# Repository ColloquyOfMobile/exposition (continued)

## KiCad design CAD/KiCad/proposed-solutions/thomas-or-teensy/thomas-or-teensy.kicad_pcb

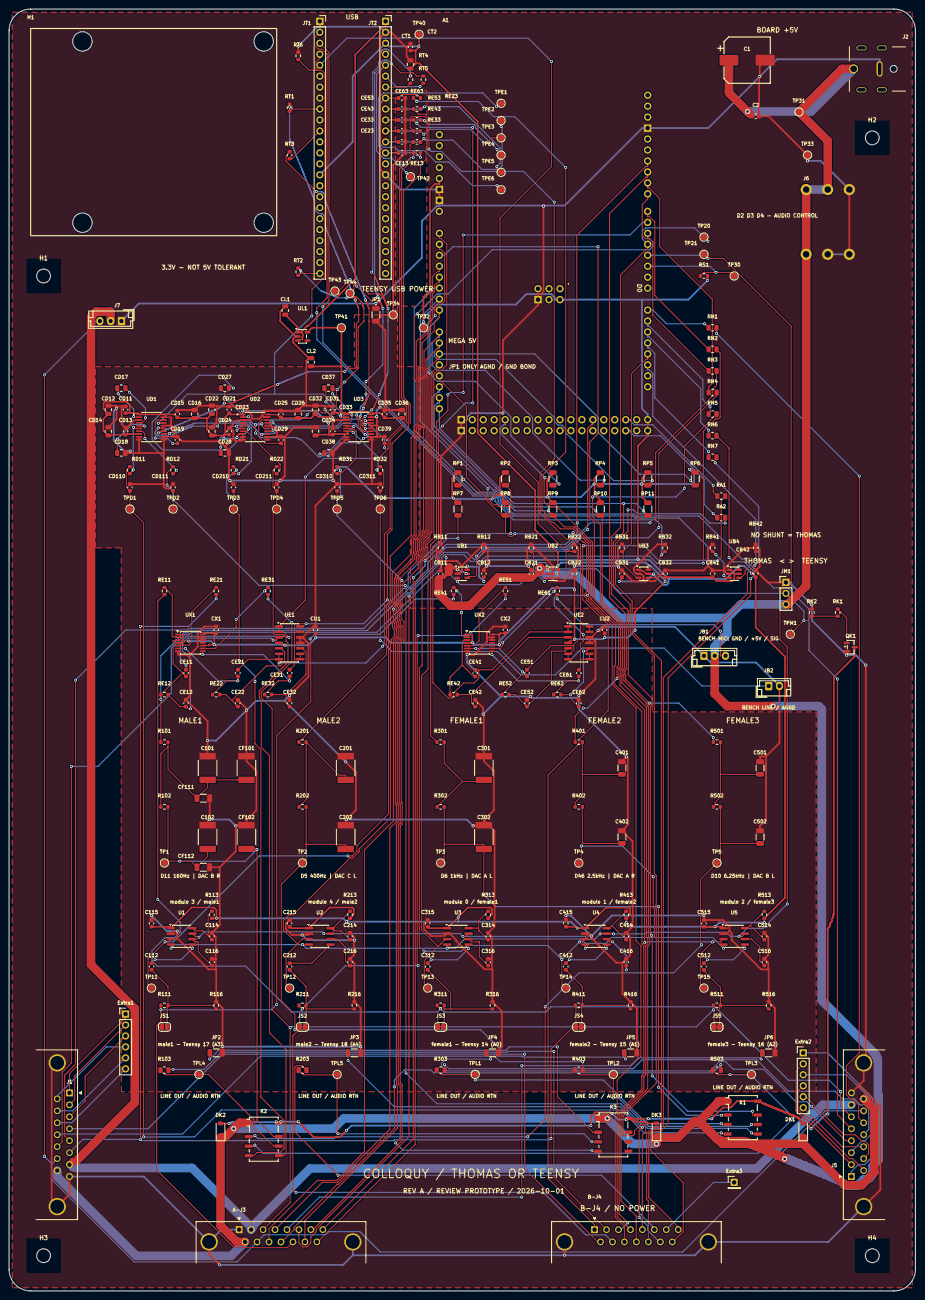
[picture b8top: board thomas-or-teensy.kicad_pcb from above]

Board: 4 copper layers, 210.0 x 297.0 mm, 290 parts (0 on the bottom side), 192 nets.

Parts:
A1: Arduino Mega 2560; Arduino_Mega2560_R3_Shield
A-J3: DSUB-15; DSUB-15_Pins_Horizontal_P2.77x2.84mm_EdgePinOffset4.94mm_Ho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
B-J4: DSUB-15; DSUB-15_Pins_Horizontal_P2.77x2.84mm_EdgePinOffset4.94mm_Ho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
C1: 470uF 25V; CP_Elec_10x10.5
C2, C112, C115, C116, C212, C215, C216, C312, C315, C316, C412, C415, C416, C512, C515, C516: 100nF; C_0603_1608Metric
C101, C102, C201, C202: 220nF PPS 5%; PPS_6041
C114, C214, C314, C414, C514: 33pF C0G; C_0603_1608Metric
C301, C302: 150nF PPS 5%; PPS_6041
C401, C402: 47nF C0G 5%; C_1206_3216Metric
C501, C502: 10nF C0G 5%; C_1206_3216Metric
CB11, CB12, CB21, CB22, CB31, CB32, CB41, CB42: 100nF; C_0603_1608Metric
CD11, CD13, CD15, CD19, CD21, CD23, CD25, CD29, CD31, CD33, CD35, CD39: 100nF; C_0603_1608Metric
CD12, CD14, CD16, CD22, CD24, CD26, CD32, CD34, CD36: 10uF; C_0805_2012Metric
CD17, CD18, CD27, CD28, CD37, CD38: 2.2uF; C_0805_2012Metric
CD110, CD111, CD210, CD211, CD310, CD311: 2.2nF C0G; C_0603_1608Metric
CE11, CE21, CE31, CE41, CE51, CE61: 2.2nF C0G; C_0603_1608Metric
CE12, CE13, CE22, CE23, CE32, CE33, CE42, CE43, CE52, CE53, CE62, CE63: 1nF C0G; C_0603_1608Metric
CF101, CF102: 220nF PPS 5%; PPS_6041
CF111, CF112: 30nF C0G 5%; C_1206_3216Metric
CL1, CL2: 10uF; C_0805_2012Metric
CT1: 100nF; C_0603_1608Metric
CT2: 10uF; C_0805_2012Metric
CU1, CU2: 100nF; C_0603_1608Metric
CX1, CX2: 100nF; C_0603_1608Metric
DK1, DK2, DK3: 1N4148W; D_SOD-123
Extra1, Extra2: 1x6 header; PinHeader_1x06_P2.54mm_Vertical
Extra3: 1x1 pad; PinHeader_1x01_P2.54mm_Vertical
H1, H2, H3, H4: M3 3.2mm NPTH; MountingHole_3.2mm_M3
J1, J5: DSUB-15; DSUB-15_Pins_Horizontal_P2.77x2.84mm_EdgePinOffset4.94mm_Ho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
J2: DC jack; PJ-082BH_jack_10A
J6: screw bridge; screw_brigde
J7: JST EH 3; JST_EH_B3B-EH-A_1x03_P2.50mm_Vertical
JB1: BENCH MIC GND +5V SIGNAL; JST_EH_B3B-EH-A_1x03_P2.50mm_Vertical
JB2: BENCH LINE / AGND; JST_EH_B2B-EH-A_1x02_P2.50mm_Vertical
JM1: THOMAS / MODE / TEENSY; PinHeader_1x03_P2.54mm_Vertical
JP1, JP2, JP3, JP4, JP5, JP6: 0R; R_1206_3216Metric
JS1, JS2, JS3, JS4, JS5: ATTEN BYPASS (OPEN); SolderJumper-2_P1.3mm_Open_RoundedPad1.0x1.5mm
JT1: Teensy 4.1 LEFT; PinSocket_1x24_P2.54mm_Vertical
JT2: Teensy 4.1 RIGHT; PinSocket_1x24_P2.54mm_Vertical
K1, K2, K3: G6K-2F-Y DC5; Relay_DPDT_Omron_G6K-2F-Y
M1: U2D2; u2d2_mounting
QK1: 2N7002; SOT-23
R101, R102, R501, R502: 2K2; R_0603_1608Metric
R103, R203, R303, R403, R503: 100R; R_0805_2012Metric
R111, R211, R311, R411, R511: 47K; R_0603_1608Metric
R113, R213, R313, R413, R513: 200K 1%; R_0603_1608Metric
R116, R216, R316, R416, R516: 6K8; R_0603_1608Metric
R201, R202: 2K; R_0603_1608Metric
R301, R302: 1K2; R_0603_1608Metric
R401, R402: 1K8; R_0603_1608Metric
RA1, RA2: 330R; R_0805_2012Metric
RB11, RB12, RB21, RB22, RB31, RB32, RB41, RB42: 100K; R_0603_1608Metric
RD11, RD12, RD21, RD22, RD31, RD32: 470R; R_0603_1608Metric
RE11, RE12, RE21, RE22, RE31, RE32, RE41, RE42, RE51, RE52, RE61, RE62: 10K 1%; R_0603_1608Metric
RE13, RE23, RE33, RE43, RE53, RE63: 100R; R_0603_1608Metric
RK1: 100R; R_0603_1608Metric
RK2: 100K; R_0603_1608Metric
RN1, RN2, RN3, RN4, RN5, RN6, RN7: 330R; R_0805_2012Metric
RP1, RP2, RP3, RP4, RP5, RP6, RP7, RP8, RP9, RP10, RP11: 10K provisional; R_1206_3216Metric
RS1: 10K; R_0603_1608Metric
RT1, RT2, RT3, RT4, RT5: 33R; R_0603_1608Metric
RT6: 10K; R_0603_1608Metric
TP1, TP2, TP3, TP4, TP5, TP11, TP12, TP13, TP14, TP15, TP20, TP21, TP30, TP31, TP32, TP33, TP34: test pad; TestPoint_Pad_D1.5mm
TP40: TEENSY_3V3; TestPoint_Pad_D1.5mm
TP41: DAC_3V3; TestPoint_Pad_D1.5mm
TP42: TEENSY_A8; TestPoint_Pad_D1.5mm
TP43: BCLK; TestPoint_Pad_D1.5mm
TP44: LRCLK; TestPoint_Pad_D1.5mm
TPD1: female1/dac; TestPoint_Pad_D1.5mm
TPD2: female2/dac; TestPoint_Pad_D1.5mm
TPD3: female3/dac; TestPoint_Pad_D1.5mm
TPD4: male1/dac; TestPoint_Pad_D1.5mm
TPD5: male2/dac; TestPoint_Pad_D1.5mm
TPD6: bench/dac; TestPoint_Pad_D1.5mm
TPE1: female1/adc; TestPoint_Pad_D1.5mm
TPE2: female2/adc; TestPoint_Pad_D1.5mm
TPE3: female3/adc; TestPoint_Pad_D1.5mm
TPE4: male1/adc; TestPoint_Pad_D1.5mm
TPE5: male2/adc; TestPoint_Pad_D1.5mm
TPE6: bench/adc; TestPoint_Pad_D1.5mm
TPL1: female1/selected; TestPoint_Pad_D1.5mm
TPL2: female2/selected; TestPoint_Pad_D1.5mm
TPL3: female3/selected; TestPoint_Pad_D1.5mm
TPL4: male1/selected; TestPoint_Pad_D1.5mm
TPL5: male2/selected; TestPoint_Pad_D1.5mm
TPM1: MODE; TestPoint_Pad_D1.5mm
U1, U2, U3, U4, U5: MSGEQ7N; SOIC-8_3.9x4.9mm_P1.27mm
UB1, UB2, UB3, UB4: SN74LVC1T45DBVR; SOT-23-6
UD1, UD2, UD3: PCM5102APWR; TSSOP-20_4.4x6.5mm_P0.65mm
UE1, UE2: MCP6004-I/SL; SOIC-14_3.9x8.7mm_P1.27mm
UL1: TLV75533PDBVR; SOT-23-5
UX1, UX2: TMUX1511PWR; TSSOP-14_4.4x5mm_P0.65mm

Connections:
+5V: A-J3.9, C1.1, C2.1, CB11.1, CB21.1, DK1.1, DK2.1, DK3.1, J1.15, J2.1, J5.15, J6.3, J6.5, J6.6, JB1.2, JM1.3, K1.1, K2.1, K3.1, TP31.1, UB1.1, UB1.5, UB2.1, UB2.5
+12V: A-J3.2, J1.7, J5.7, J7.2
AGND: C101.2, C102.2, C114.2, C115.2, C116.2, C201.2, C202.2, C214.2, C215.2, C216.2, C301.2, C302.2, C314.2, C315.2, C316.2, C401.2, C402.2, C414.2, C415.2, C416.2, C501.2, C502.2, C514.2, C515.2, C516.2, CD11.2, CD12.2, CD13.2, CD14.2, CD15.2, CD16.2, CD18.2, CD19.2, CD21.2, CD22.2, CD23.2, CD24.2, CD25.2, CD26.2, CD28.2, CD29.2, CD31.2, CD32.2, CD33.2, CD34.2, CD35.2, CD36.2, CD38.2, CD39.2, CD110.2, CD111.2, CD210.2, CD211.2, CD310.2, CD311.2, CE12.2, CE13.2, CE22.2, CE23.2, CE32.2, CE33.2, CE42.2, CE43.2, CE52.2, CE53.2, CE62.2, CE63.2, CF101.2, CF102.2, CF111.2, CF112.2, CL1.2, CL2.2, CU1.2, CU2.2, CX1.2, CX2.2, JB1.1, JB2.2, JP1.1, JP2.2, JP3.2, JP4.2, JP5.2, JP6.2, R116.2, R216.2, R316.2, R416.2, R516.2, RP1.2, RP2.2, RP3.2, RP4.2, RP5.2, RP6.2, RP7.2, RP8.2, RP9.2, RP10.2, RP11.2, TP34.1, U1.2, U2.2, U3.2, U4.2, U5.2, UD1.3, UD1.9, UD1.10, UD1.11, UD1.12, UD1.16, UD1.19, UD2.3, UD2.9, UD2.10, UD2.11, UD2.12, UD2.16, UD2.19, UD3.3, UD3.9, UD3.10, UD3.11, UD3.12, UD3.16, UD3.19, UE1.11, UE1.12, UE2.11, UE2.12, UL1.2, UX1.7, UX1.12, UX1.13, UX2.7, UX2.12, UX2.13
BCLK: RT5.2, TP43.1, UD1.13, UD2.13, UD3.13
BCLK_raw: JT2.6, RT5.1
COIL_GATE: QK1.1, RK1.2
COIL_LOW: DK1.2, DK2.2, DK3.2, K1.8, K2.8, K3.8, QK1.3
DAC_3V3: CD11.1, CD12.1, CD13.1, CD14.1, CD15.1, CD16.1, CD21.1, CD22.1, CD23.1, CD24.1, CD25.1, CD26.1, CD31.1, CD32.1, CD33.1, CD34.1, CD35.1, CD36.1, CL2.1, TP41.1, UD1.1, UD1.8, UD1.20, UD2.1, UD2.8, UD2.20, UD3.1, UD3.8, UD3.20, UL1.5
DAC_A/CAPM: CD17.2, UD1.4
DAC_A/CAPP: CD17.1, UD1.2
DAC_A/LDOO: CD19.1, UD1.18
DAC_A/VNEG: CD18.1, UD1.5
DAC_B/CAPM: CD27.2, UD2.4
DAC_B/CAPP: CD27.1, UD2.2
DAC_B/LDOO: CD29.1, UD2.18
DAC_B/VNEG: CD28.1, UD2.5
DAC_C/CAPM: CD37.2, UD3.4
DAC_C/CAPP: CD37.1, UD3.2
DAC_C/LDOO: CD39.1, UD3.18
DAC_C/VNEG: CD38.1, UD3.5
DAC_XSMT: JT1.4, RT6.1, UD1.17, UD2.17, UD3.17
GND: A1.GND1, A1.GND2, A1.GND3, A1.GND4, A1.GND5, A1.GND6, A-J3.0, A-J3.1, B-J4.0, C1.2, C2.2, CB11.2, CB12.2, CB21.2, CB22.2, CB31.2, CB32.2, CB41.2, CB42.2, CT1.2, CT2.2, J1.0, J1.8, J2.2, J5.0, J5.8, J6.1, J6.2, J6.4, J7.1, JM1.1, JP1.2, JT1.1, JT2.2, JT2.15, QK1.2, RB11.2, RB12.2, RB21.2, RB22.2, RB31.2, RB32.2, RB41.2, RB42.2, RK2.2, RT6.2, TP33.1, UB1.2, UB2.2, UB3.2, UB4.2
I2S_A: RT1.2, UD1.14
I2S_A_raw: JT1.9, RT1.1
I2S_B: RT2.2, UD2.14
I2S_B_raw: JT1.24, RT2.1
I2S_C: RT3.2, UD3.14
I2S_C_raw: JT1.11, RT3.1
LRCLK: RT4.2, TP44.1, UD1.15, UD2.15, UD3.15
LRCLK_raw: JT2.7, RT4.1
MEGA_5V: A1.5V1, A1.5V2, A1.5V3, A1.5V4, C115.1, C215.1, C315.1, C415.1, C515.1, CB12.1, CB31.1, CB42.1, R113.1, R213.1, R313.1, R413.1, R513.1, RS1.2, TP32.1, U1.1, U2.1, U3.1, U4.1, U5.1, UB1.6, UB3.1, UB3.5, UB4.6
MODE: JM1.2, RB11.1, RB21.1, RK1.1, RK2.1, TPM1.1, UB1.3, UB2.3
MODE_MEGA: A1.D30, RB12.1, UB1.4
MODE_TEENSY: JT1.5, RB22.1, UB2.4
TEENSY_3V3: CB22.1, CB32.1, CB41.1, CT1.1, CT2.1, CU1.1, CU2.1, CX1.1, CX2.1, JT1.15, JT2.3, TP40.1, UB2.6, UB3.6, UB4.1, UB4.5, UE1.4, UE2.4, UX1.1, UX1.4, UX1.10, UX1.14, UX2.1, UX2.4, UX2.10, UX2.14
TEENSY_A8: JT2.5, TP42.1
TEENSY_VIN: CL1.1, JT2.1, UL1.1, UL1.3
amp shutdown: A1.D2, RS1.1, TP30.1
analyser/reset: A1.D3, TP21.1, U1.7, U2.7, U3.7, U4.7, U5.7
analyser/strobe: A1.D4, TP20.1, U1.4, U2.4, U3.4, U4.4, U5.4
bench/adc: CE63.1, JT2.8, RE63.2, TPE6.1
bench/buffer: CE61.2, RE63.1, UE2.8, UE2.9
bench/dac: CD311.1, JB2.1, RD32.2, TPD6.1
bench/dac raw: RD32.1, UD3.7
bench/filter: CE62.1, RE62.2, UE2.10
bench/isolator in: RE61.2, UX2.9
bench/microphone: JB1.3, RE61.1
bench/mid: CE61.1, RE62.1, UX2.8
centre/spare1: B-J4.7, Extra3.1
dxl_data: A-J3.10, J1.14, J5.14, J7.3
female1/adc: CE13.1, JT2.13, RE13.2, TPE1.1
female1/analyser out: A1.A0, TP13.1, U3.3
female1/audio return: J5.4, JP4.1
female1/buffer: CE11.2, RE13.1, UE1.1, UE1.2
female1/dac: CD110.1, K1.4, RD11.2, TPD1.1
female1/dac raw: RD11.1, UD1.6
female1/filter: CE12.1, RE12.2, UE1.3
female1/filter mid: C301.1, R301.2, R302.1
female1/filter out: C302.1, K1.2, R302.2, TP3.1
female1/internal reference: C316.1, U3.6
female1/isolator in: RE11.2, UX1.2
female1/line out: J5.12, R303.2
female1/mic attenuated: C312.1, JS3.2, R311.2, R316.1
female1/microphone: J5.6, JS3.1, R311.1, RE11.1
female1/mid: CE11.1, RE12.1, UX1.3
female1/msgeq input: C312.2, U3.5
female1/neopixel: J5.13, RN1.2
female1/neopixel/driven: A1.D14, RN1.1
female1/oscillator: C314.1, R313.2, U3.8
female1/photosensor: A1.A5, J5.5, RP1.1
female1/selected: K1.3, R303.1, TPL1.1
female1/spare1: Extra2.1, J5.1
female1/spare2: Extra2.2, J5.2
female1/spare3: Extra2.3, J5.3
female1/spare4: Extra2.4, J5.9
female1/spare5: Extra2.5, J5.10
female1/spare6: Extra2.6, J5.11
female1/tone: A1.D6, R301.1
female2/adc: CE23.1, JT2.12, RE23.2, TPE2.1
female2/analyser out: A1.A1, TP14.1, U4.3
female2/audio return: J1.4, JP5.1
female2/buffer: CE21.2, RE23.1, UE1.6, UE1.7
female2/dac: CD111.1, K1.5, RD12.2, TPD2.1
female2/dac raw: RD12.1, UD1.7
female2/filter: CE22.1, RE22.2, UE1.5
female2/filter mid: C401.1, R401.2, R402.1
female2/filter out: C402.1, K1.7, R402.2, TP4.1
female2/internal reference: C416.1, U4.6
female2/isolator in: RE21.2, UX1.5
female2/line out: J1.12, R403.2
female2/mic attenuated: C412.1, JS4.2, R411.2, R416.1
female2/microphone: J1.6, JS4.1, R411.1, RE21.1
female2/mid: CE21.1, RE22.1, UX1.6
female2/msgeq input: C412.2, U4.5
female2/neopixel: J1.13, RN2.2
female2/neopixel/driven: A1.D7, RN2.1
female2/oscillator: C414.1, R413.2, U4.8
female2/photosensor: A1.A6, J1.5, RP2.1
female2/selected: K1.6, R403.1, TPL2.1
female2/spare1: Extra1.1, J1.1
female2/spare2: Extra1.2, J1.2
female2/spare3: Extra1.3, J1.3
female2/spare4: Extra1.4, J1.9
female2/spare5: Extra1.5, J1.10
female2/spare6: Extra1.6, J1.11
female2/tone: A1.D46, R401.1
female3/adc: CE33.1, JT2.11, RE33.2, TPE3.1
female3/analyser out: A1.A2, TP15.1, U5.3
female3/audio return: A-J3.5, JP6.1
female3/buffer: CE31.2, RE33.1, UE1.8, UE1.9
female3/dac: CD210.1, K2.4, RD21.2, TPD3.1
female3/dac raw: RD21.1, UD2.6
female3/filter: CE32.1, RE32.2, UE1.10
female3/filter mid: C501.1, R501.2, R502.1
female3/filter out: C502.1, K2.2, R502.2, TP5.1
female3/internal reference: C516.1, U5.6
female3/isolator in: RE31.2, UX1.9
female3/line out: A-J3.12, R503.2
female3/mic attenuated: C512.1, JS5.2, R511.2, R516.1
female3/microphone: A-J3.3, JS5.1, R511.1, RE31.1
female3/mid: CE31.1, RE32.1, UX1.8
female3/msgeq input: C512.2, U5.5
female3/neopixel: A-J3.11, RN3.2
female3/neopixel/driven: A1.D8, RN3.1
female3/oscillator: C514.1, R513.2, U5.8
female3/photosensor: A1.A7, A-J3.4, RP3.1
female3/selected: K2.3, R503.1, TPL3.1
female3/tone: A1.D10, R501.1
link/mega_tx: A1.D18, RB31.1, UB3.3
link/teensy_tx: JT1.3, RB41.1, UB4.3
link/to_mega: A1.D19, RB42.1, UB4.4
link/to_teensy: JT1.2, RB32.1, UB3.4
male1/adc: CE43.1, JT2.10, RE43.2, TPE4.1
male1/analyser out: A1.A3, TP11.1, U1.3
male1/audio return: B-J4.2, JP2.1
male1/aux: B-J4.1, RA1.2
male1/aux driven: A1.D24, RA1.1
male1/bar neopixel: B-J4.15, RN6.2
male1/bar neopixel/driven: A1.D16, RN6.1
male1/buffer: CE41.2, RE43.1, UE2.1, UE2.2
male1/dac: CD211.1, K2.5, RD22.2, TPD4.1
male1/dac raw: RD22.1, UD2.7
male1/filter: CE42.1, RE42.2, UE2.3
male1/filter mid: C101.1, CF101.1, CF111.1, R101.2, R102.1
male1/filter out: C102.1, CF102.1, CF112.1, K2.7, R102.2, TP1.1
male1/internal reference: C116.1, U1.6
male1/isolator in: RE41.2, UX2.2
male1/line out: B-J4.9, R103.2
male1/mic attenuated: C112.1, JS1.2, R111.2, R116.1
male1/microphone: A-J3.13, JS1.1, R111.1, RE41.1
male1/mid: CE41.1, RE42.1, UX2.3
male1/msgeq input: C112.2, U1.5
male1/neopixel: A-J3.6, RN4.2
male1/neopixel/driven: A1.D9, RN4.1
male1/oscillator: C114.1, R113.2, U1.8
male1/photosensor/A: A1.A8, A-J3.14, RP4.1
male1/photosensor/B: A1.A9, A-J3.7, RP5.1
male1/photosensor/C: A1.A10, A-J3.15, RP6.1
male1/photosensor/D: A1.A11, A-J3.8, RP7.1
male1/selected: K2.6, R103.1, TPL4.1
male1/tone: A1.D11, R101.1
male2/adc: CE53.1, JT2.9, RE53.2, TPE5.1
male2/analyser out: A1.A4, TP12.1, U2.3
male2/audio return: B-J4.14, JP3.1
male2/aux: B-J4.13, RA2.2
male2/aux driven: A1.D25, RA2.1
male2/bar neopixel: B-J4.8, RN7.2
male2/bar neopixel/driven: A1.D17, RN7.1
male2/buffer: CE51.2, RE53.1, UE2.6, UE2.7
male2/dac: CD310.1, K3.4, RD31.2, TPD5.1
male2/dac raw: RD31.1, UD3.6
male2/filter: CE52.1, RE52.2, UE2.5
male2/filter mid: C201.1, R201.2, R202.1
male2/filter out: C202.1, K3.2, R202.2, TP2.1
male2/internal reference: C216.1, U2.6
male2/isolator in: RE51.2, UX2.5
male2/line out: B-J4.6, R203.2
male2/mic attenuated: C212.1, JS2.2, R211.2, R216.1
male2/microphone: B-J4.10, JS2.1, R211.1, RE51.1
male2/mid: CE51.1, RE52.1, UX2.6
male2/msgeq input: C212.2, U2.5
male2/neopixel: B-J4.3, RN5.2
male2/neopixel/driven: A1.D15, RN5.1
male2/oscillator: C214.1, R213.2, U2.8
male2/photosensor/A: A1.A12, B-J4.11, RP8.1
male2/photosensor/B: A1.A13, B-J4.4, RP9.1
male2/photosensor/C: A1.A14, B-J4.12, RP10.1
male2/photosensor/D: A1.A15, B-J4.5, RP11.1
male2/selected: K3.3, R203.1, TPL5.1
male2/tone: A1.D5, R201.1
spare1/buffer: UE1.13, UE1.14
spare2/buffer: UE2.13, UE2.14

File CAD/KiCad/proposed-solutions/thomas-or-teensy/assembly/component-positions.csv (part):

Ref,Val,Package,PosX,PosY,Rot,Side
"A-J3","DSUB-15","DSUB-15_Pins_Horizontal_P2.77x2.84mm_EdgePinOffset4.94mm_Housed_MountingHolesOffset4.94mm",97.305000,-334.960000,0.000000,top
"A1","Arduino Mega 2560","Arduino_Mega2560_R3_Shield",141.160000,-53.320000,-90.000000,top
"B-J4","DSUB-15","DSUB-15_Pins_Horizontal_P2.77x2.84mm_EdgePinOffset4.94mm_Housed_MountingHolesOffset4.94mm",179.655000,-334.960000,0.000000,top
"C1","470uF 25V","CP_Elec_10x10.5",215.000000,-64.000000,0.000000,top
"C2","100nF","C_0603_1608Metric",217.000000,-77.000000,0.000000,top
"C101","220nF PPS 5%","PPS_6041",90.000000,-228.000000,90.000000,top
"C102","220nF PPS 5%","PPS_6041",90.000000,-244.000000,90.000000,top
"C112","100nF","C_0603_1608Metric",77.000000,-274.000000,90.000000,top
"C114","33pF C0G","C_0603_1608Metric",91.000000,-267.000000,90.000000,top
"C115","100nF","C_0603_1608Metric",77.000000,-264.000000,90.000000,top
"C116","100nF","C_0603_1608Metric",91.000000,-273.000000,90.000000,top
"C201","220nF PPS 5%","PPS_6041",122.000000,-228.000000,90.000000,top
"C202","220nF PPS 5%","PPS_6041",122.000000,-244.000000,90.000000,top
"C212","100nF","C_0603_1608Metric",109.000000,-274.000000,90.000000,top
"C214","33pF C0G","C_0603_1608Metric",123.000000,-267.000000,90.000000,top
"C215","100nF","C_0603_1608Metric",109.000000,-264.000000,90.000000,top
"C216","100nF","C_0603_1608Metric",123.000000,-273.000000,90.000000,top
"C301","150nF PPS 5%","PPS_6041",154.000000,-228.000000,90.000000,top
"C302","150nF PPS 5%","PPS_6041",154.000000,-244.000000,90.000000,top
"C312","100nF","C_0603_1608Metric",141.000000,-274.000000,90.000000,top
"C314","33pF C0G","C_0603_1608Metric",155.000000,-267.000000,90.000000,top
"C315","100nF","C_0603_1608Metric",141.000000,-264.000000,90.000000,top
"C316","100nF","C_0603_1608Metric",155.000000,-273.000000,90.000000,top
"C401","47nF C0G 5%","C_1206_3216Metric",186.000000,-228.000000,90.000000,top
"C402","47nF C0G 5%","C_1206_3216Metric",186.000000,-244.000000,90.000000,top
"C412","100nF","C_0603_1608Metric",173.000000,-274.000000,90.000000,top
"C414","33pF C0G","C_0603_1608Metric",187.000000,-267.000000,90.000000,top
"C415","100nF","C_0603_1608Metric",173.000000,-264.000000,90.000000,top
"C416","100nF","C_0603_1608Metric",187.000000,-273.000000,90.000000,top
"C501","10nF C0G 5%","C_1206_3216Metric",218.000000,-228.000000,90.000000,top
"C502","10nF C0G 5%","C_1206_3216Metric",218.000000,-244.000000,90.000000,top
"C512","100nF","C_0603_1608Metric",205.000000,-274.000000,90.000000,top
"C514","33pF C0G","C_0603_1608Metric",219.000000,-267.000000,90.000000,top
"C515","100nF","C_0603_1608Metric",205.000000,-264.000000,90.000000,top
"C516","100nF","C_0603_1608Metric",219.000000,-273.000000,90.000000,top
"CB11","100nF","C_0603_1608Metric",144.000000,-183.000000,90.000000,top
"CB12","100nF","C_0603_1608Metric",154.000000,-183.000000,90.000000,top
"CB21","100nF","C_0603_1608Metric",165.000000,-183.000000,90.000000,top
"CB22","100nF","C_0603_1608Metric",175.000000,-183.000000,90.000000,top
"CB31","100nF","C_0603_1608Metric",186.000000,-183.000000,90.000000,top
"CB32","100nF","C_0603_1608Metric",196.000000,-183.000000,90.000000,top
"CB41","100nF","C_0603_1608Metric",207.000000,-183.000000,90.000000,top
"CB42","100nF","C_0603_1608Metric",217.000000,-183.000000,90.000000,top
"CD11","100nF","C_0603_1608Metric",71.000000,-145.000000,90.000000,top
"CD12","10uF","C_0805_2012Metric",67.000000,-145.000000,90.000000,top
"CD13","100nF","C_0603_1608Metric",71.000000,-150.000000,90.000000,top
"CD14","10uF","C_0805_2012Metric",67.000000,-150.000000,90.000000,top
"CD15","100nF","C_0603_1608Metric",83.000000,-146.000000,90.000000,top
"CD16","10uF","C_0805_2012Metric",87.000000,-146.000000,90.000000,top
"CD17","2.2uF","C_0805_2012Metric",70.000000,-140.000000,0.000000,top
"CD18","2.2uF","C_0805_2012Metric",70.000000,-155.000000,0.000000,top
"CD19","100nF","C_0603_1608Metric",83.000000,-152.000000,90.000000,top
"CD21","100nF","C_0603_1608Metric",95.000000,-145.000000,90.000000,top
"CD22","10uF","C_0805_2012Metric",91.000000,-145.000000,90.000000,top
"CD23","100nF","C_0603_1608Metric",95.000000,-150.000000,90.000000,top
"CD24","10uF","C_0805_2012Metric",91.000000,-150.000000,90.000000,top
"CD25","100nF","C_0603_1608Metric",107.000000,-146.000000,90.000000,top
"CD26","10uF","C_0805_2012Metric",111.000000,-146.000000,90.000000,top
"CD27","2.2uF","C_0805_2012Metric",94.000000,-140.000000,0.000000,top
"CD28","2.2uF","C_0805_2012Metric",94.000000,-155.000000,0.000000,top
"CD29","100nF","C_0603_1608Metric",107.000000,-152.000000,90.000000,top
"CD31","100nF","C_0603_1608Metric",119.000000,-145.000000,90.000000,top
"CD32","10uF","C_0805_2012Metric",115.000000,-145.000000,90.000000,top
"CD33","100nF","C_0603_1608Metric",119.000000,-150.000000,90.000000,top
"CD34","10uF","C_0805_2012Metric",115.000000,-150.000000,90.000000,top
"CD35","100nF","C_0603_1608Metric",131.000000,-146.000000,90.000000,top
"CD36","10uF","C_0805_2012Metric",135.000000,-146.000000,90.000000,top
"CD37","2.2uF","C_0805_2012Metric",118.000000,-140.000000,0.000000,top
"CD38","2.2uF","C_0805_2012Metric",118.000000,-155.000000,0.000000,top
"CD39","100nF","C_0603_1608Metric",131.000000,-152.000000,90.000000,top
"CD110","2.2nF C0G","C_0603_1608Metric",72.000000,-163.000000,90.000000,top
"CD111","2.2nF C0G","C_0603_1608Metric",82.000000,-163.000000,90.000000,top
"CD210","2.2nF C0G","C_0603_1608Metric",96.000000,-163.000000,90.000000,top
"CD211","2.2nF C0G","C_0603_1608Metric",106.000000,-163.000000,90.000000,top
"CD310","2.2nF C0G","C_0603_1608Metric",120.000000,-163.000000,90.000000,top
"CD311","2.2nF C0G","C_0603_1608Metric",130.000000,-163.000000,90.000000,top
"CE11","2.2nF C0G","C_0603_1608Metric",85.000000,-206.000000,90.000000,top
"CE12","1nF C0G","C_0603_1608Metric",85.000000,-213.000000,90.000000,top
"CE13","1nF C0G","C_0603_1608Metric",135.000000,-85.480000,0.000000,top
"CE21","2.2nF C0G","C_0603_1608Metric",97.000000,-206.000000,90.000000,top
"CE22","1nF C0G","C_0603_1608Metric",97.000000,-213.000000,90.000000,top
"CE23","1nF C0G","C_0603_1608Metric",135.000000,-82.940000,0.000000,top
"CE31","2.2nF C0G","C_0603_1608Metric",109.000000,-206.000000,90.000000,top
"CE32","1nF C0G","C_0603_1608Metric",109.000000,-213.000000,90.000000,top
"CE33","1nF C0G","C_0603_1608Metric",135.000000,-80.400000,0.000000,top
"CE41","2.2nF C0G","C_0603_1608Metric",152.000000,-206.000000,90.000000,top
"CE42","1nF C0G","C_0603_1608Metric",152.000000,-213.000000,90.000000,top
"CE43","1nF C0G","C_0603_1608Metric",135.000000,-77.860000,0.000000,top
"CE51","2.2nF C0G","C_0603_1608Metric",164.000000,-206.000000,90.000000,top
"CE52","1nF C0G","C_0603_1608Metric",164.000000,-213.000000,90.000000,top
"CE53","1nF C0G","C_0603_1608Metric",135.000000,-75.320000,0.000000,top
"CE61","2.2nF C0G","C_0603_1608Metric",176.000000,-206.000000,90.000000,top
"CE62","1nF C0G","C_0603_1608Metric",176.000000,-213.000000,90.000000,top
"CE63","1nF C0G","C_0603_1608Metric",135.000000,-72.780000,0.000000,top
"CF101","220nF PPS 5%","PPS_6041",99.000000,-228.000000,90.000000,top
"CF102","220nF PPS 5%","PPS_6041",99.000000,-244.000000,90.000000,top
"CF111","30nF C0G 5%","C_1206_3216Metric",89.000000,-235.000000,0.000000,top
"CF112","30nF C0G 5%","C_1206_3216Metric",89.000000,-251.000000,0.000000,top
"CL1","10uF","C_0805_2012Metric",108.000000,-122.000000,90.000000,top
"CL2","10uF","C_0805_2012Metric",114.000000,-134.000000,90.000000,top
"CT1","100nF","C_0603_1608Metric",137.000000,-61.000000,90.000000,top
"CT2","10uF","C_0805_2012Metric",137.000000,-65.000000,90.000000,top
"CU1","100nF","C_0603_1608Metric",115.000000,-196.000000,90.000000,top
"CU2","100nF","C_0603_1608Metric",182.000000,-196.000000,90.000000,top
"CX1","100nF","C_0603_1608Metric",92.000000,-196.000000,90.000000,top
"CX2","100nF","C_0603_1608Metric",159.000000,-196.000000,90.000000,top
"DK1","1N4148W","D_SOD-123",228.000000,-312.000000,90.000000,top
"DK2","1N4148W","D_SOD-123",93.000000,-312.000000,90.000000,top
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
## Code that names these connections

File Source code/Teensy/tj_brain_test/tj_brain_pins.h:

/* ----------------------------------------------------------------------------
 * tj_brain_pins.h  -  Teensy 4.1 pin map of the "TJ Brain" unit board (rev A)
 *
 * One board per unit (female 1-3, male 1-2, bar). Generated from
 * CAD/KiCad/generator/brain.py - keep both in sync.
 * ----------------------------------------------------------------------------
 */
#pragma once

// ---- Dynamixel X-series TTL bus (Serial1 + direction, 74AHCT1G126 / 74LVC1G125)
#define DXL_SERIAL        Serial1   // RX1 = 0, TX1 = 1
#define DXL_DIR_PIN       2         // HIGH = transmit, LOW = receive (10k pull-down)

// ---- NeoPixel outputs (3.3V -> 5V via 74AHCT125, 330R series)
//      All four pins are Serial TX pins, usable with WS2812Serial (DMA, non blocking)
#define NP1_PIN           8         // TX2  - terminal NP1 + DA-15 pin 13 (main body strip)
#define NP2_PIN           29        // TX7  - terminal NP2 + DA-15 pin 9  (male up ring)
#define NP3_PIN           35        // TX8  - terminal NP3
#define NP4_PIN           24        // TX6  - terminal NP4

// ---- Audio
#define AUDIO_PIN         12        // tone() or MQSL -> RC low pass -> divider -> amp
#define AMP_EN_PIN        5         // TPA2005D1 shutdown (HIGH = on, 100k pull-up)
#define MIC_PIN           A2        // pin 16, MAX9814 output (clamped 0..3.3V)
#define EQ_STROBE_PIN     9         // MSGEQ7 (optional, socketed)
#define EQ_RESET_PIN      10
#define EQ_OUT_PIN        A7        // pin 21

// ---- Light sensors (0..5V sensor -> 10k/18k divider -> ADC); LM339 drives LIGHTn LEDs
#define LS1_PIN           A0        // pin 14 - DA-15 pin 5  (female photosensor / male A)
#define LS2_PIN           A1        // pin 15 - DA-15 pin 1  (male B)
#define LS3_PIN           A3        // pin 17 - DA-15 pin 2  (male C)
#define LS4_PIN           A6        // pin 20 - DA-15 pin 3  (male D)
#define AUX_PIN           A8        // pin 22 - DA-15 pin 11 (spare analog, clamped)

// ---- State LED high-side outputs (switched +5V through 150R, PWM capable)
#define STATE1_PIN        3         // JST STATE1 + DA-15 pin 10 (male backlight / beam)
#define STATE2_PIN        4         // JST STATE2

// ---- Unit identity DIP switch SW1 (switch ON pulls to GND -> use INPUT_PULLUP, invert)
#define ID0_PIN           6
#define ID1_PIN           7
#define ID2_PIN           11
#define ID3_PIN           28

// ---- Firmware status LEDs (active HIGH)
#define LED_HEARTBEAT_PIN 30
#define LED_HOST_PIN      31
#define LED_ERROR_PIN     32
#define LED_USER_PIN      37

// ---- Expansion header J2 (2x5): 3V3, 5V, SDA(18), SCL(19), 23(A9), 25(A11), 26, 27, 40(A16), 41(A17)

enum UnitId : uint8_t { UNIT_NONE = 0, UNIT_FEMALE1 = 1, UNIT_FEMALE2 = 2, UNIT_FEMALE3 = 3,
                        UNIT_MALE1 = 4, UNIT_MALE2 = 5, UNIT_BAR = 6 };

static inline uint8_t readUnitId() {
  const uint8_t pins[4] = {ID0_PIN, ID1_PIN, ID2_PIN, ID3_PIN};
  uint8_t id = 0;
  for (uint8_t i = 0; i < 4; i++) {
    pinMode(pins[i], INPUT_PULLUP);
  }
  delayMicroseconds(50);
  for (uint8_t i = 0; i < 4; i++) {
    if (digitalRead(pins[i]) == LOW) id |= (1 << i);   // switch ON = 1
  }
  return id;
}

static inline const char* unitName(uint8_t id) {
  switch (id) {
    case UNIT_FEMALE1: return "female1";
    case UNIT_FEMALE2: return "female2";
    case UNIT_FEMALE3: return "female3";
    case UNIT_MALE1:   return "male1";
    case UNIT_MALE2:   return "male2";
    case UNIT_BAR:     return "bar";
    default:           return "unknown";
  }
}

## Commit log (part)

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2026-06-30 plot threashold
